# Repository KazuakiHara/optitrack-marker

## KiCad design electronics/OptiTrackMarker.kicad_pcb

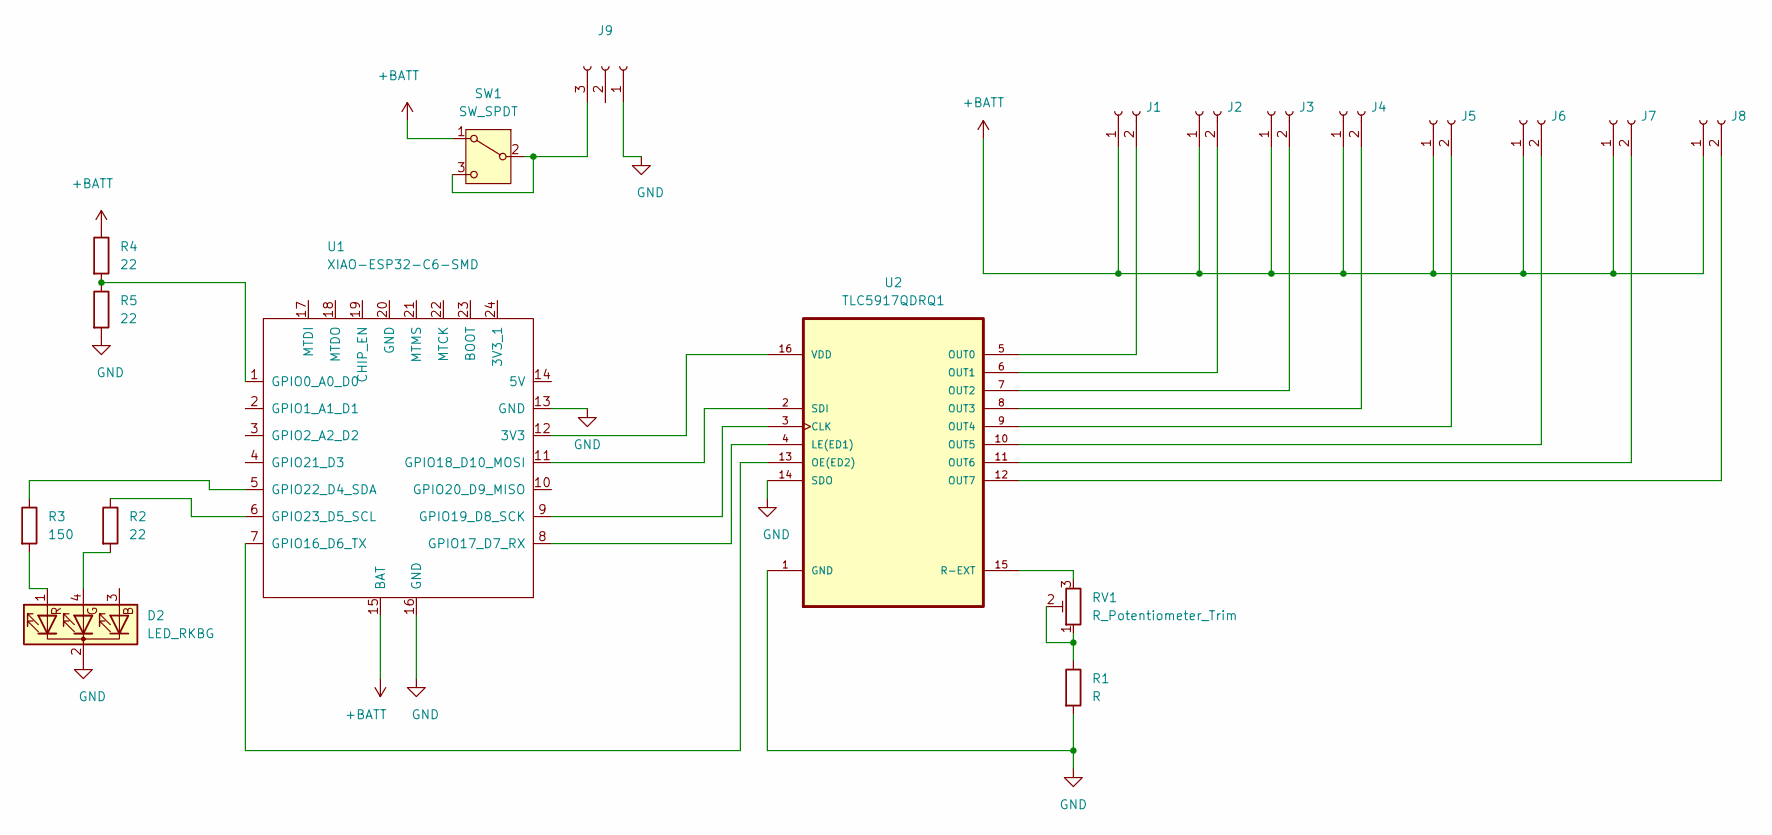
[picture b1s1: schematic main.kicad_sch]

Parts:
D2: LED_RKBG; LED_D5.0mm-4_RGB
J1, J2, J3, J4, J5, J6, J7, J8: Conn_01x02_Socket; Molex_PicoBlade_53048-0210_1x02_P1.25mm_Horizontal
J9: Conn_01x03_Socket; Molex_PicoBlade_53048-0310_1x03_P1.25mm_Horizontal
R1: R; R_0603_1608Metric_Pad0.98x0.95mm_HandSolder
R2: 22; R_Axial_DIN0207_L6.3mm_D2.5mm_P10.16mm_Horizontal
R3: 150; R_Axial_DIN0207_L6.3mm_D2.5mm_P10.16mm_Horizontal
R4, R5: 22; R_0603_1608Metric_Pad0.98x0.95mm_HandSolder
RV1: R_Potentiometer_Trim; Potentiometer_Bourns_TC33X_Vertical
SW1: SW_SPDT; SW_Slide-03_Wuerth-WS-SLTV_10x2.5x6.4_P2.54mm
U1: XIAO-ESP32-C6-SMD; XIAO-ESP32C6-SMD
U2: TLC5917QDRQ1; SOIC127P600X175-16N

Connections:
+BATT: J1.1, J2.1, J3.1, J4.1, J5.1, J6.1, J7.1, J8.1, R4.1, SW1.1 (A), U1.15 (BAT)
GND: D2.2 (K), J9.1, R1.2, R5.2, U1.13 (GND), U1.16 (GND), U2.1 (GND), U2.14 (SDO)
unnamed: D2.4 (GA), R2.2
unnamed: D2.1 (RA), R3.2
unnamed: J1.2, U2.5 (OUT0)
unnamed: J2.2, U2.6 (OUT1)
unnamed: J3.2, U2.7 (OUT2)
unnamed: J4.2, U2.8 (OUT3)
unnamed: J5.2, U2.9 (OUT4)
unnamed: J6.2, U2.10 (OUT5)
unnamed: J7.2, U2.11 (OUT6)
unnamed: J8.2, U2.12 (OUT7)
unnamed: J9.3, SW1.2 (B), SW1.3 (C)
unnamed: R1.1, RV1.1, RV1.2
unnamed: U1.12 (3V3), U2.16 (VDD)
unnamed: R4.2, R5.1, U1.1 (GPIO0_A0_D0)
unnamed: U1.7 (GPIO16_D6_TX), U2.13 (OE(ED2))
unnamed: U1.8 (GPIO17_D7_RX), U2.4 (LE(ED1))
unnamed: U1.11 (GPIO18_D10_MOSI), U2.2 (SDI)
unnamed: U1.9 (GPIO19_D8_SCK), U2.3 (CLK)
unnamed: R3.1, U1.5 (GPIO22_D4_SDA)
unnamed: R2.1, U1.6 (GPIO23_D5_SCL)
unnamed: RV1.3, U2.15 (R-EXT)

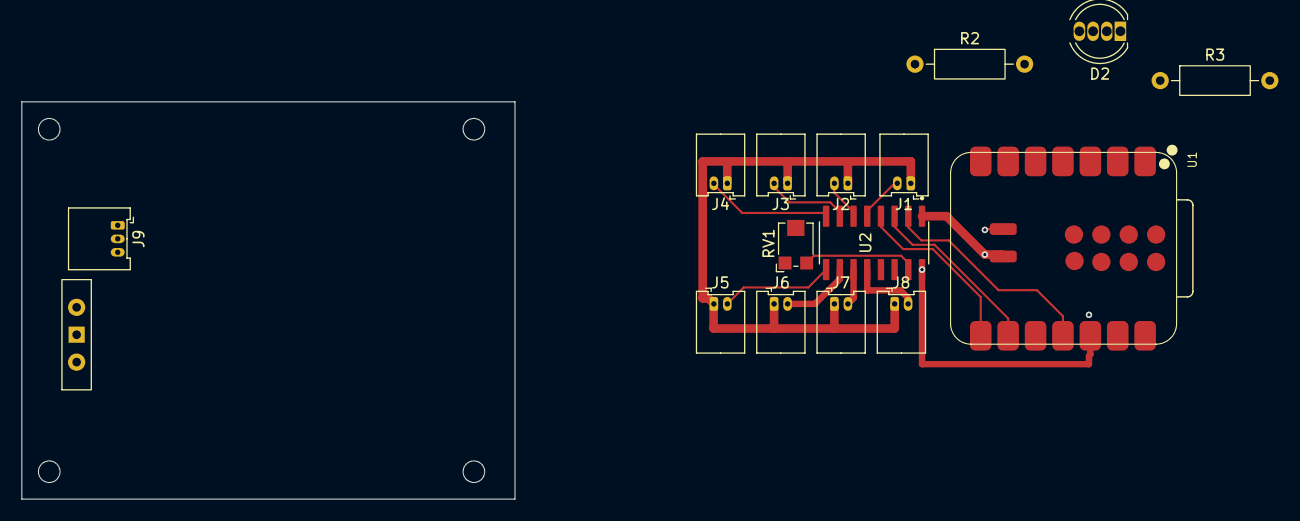
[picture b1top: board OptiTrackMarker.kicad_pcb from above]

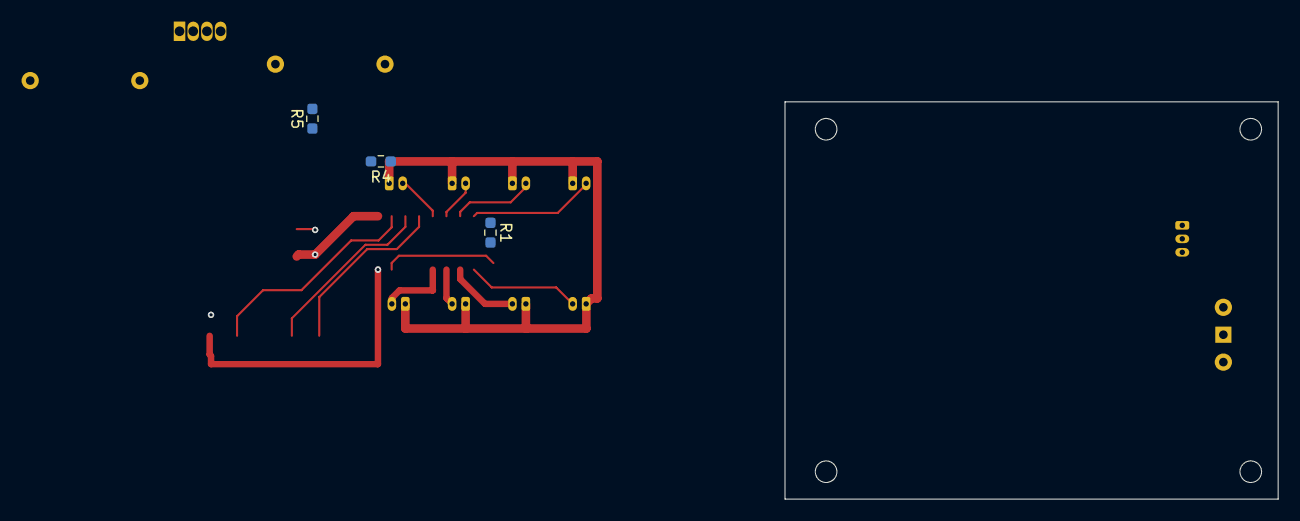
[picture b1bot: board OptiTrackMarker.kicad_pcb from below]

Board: 4 copper layers, 45.7 x 36.8 mm, 19 parts (3 on the bottom side), 23 nets.

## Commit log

2025-10-09 1st commit
2025-10-09 [WIP@ele] connector layout change
2025-10-09 [WIP] in prgress, copy real circuit..
2025-10-10 [WIP] 青色LEDで動作確認まで完了
2025-10-13 [ele] v2 layout draft
2025-10-14 [WIP]
2025-11-19 [firmware] first release version
    - just all IR-LED on
    - flick Green-LED always
    - monitoring batt, but there is only serial output
